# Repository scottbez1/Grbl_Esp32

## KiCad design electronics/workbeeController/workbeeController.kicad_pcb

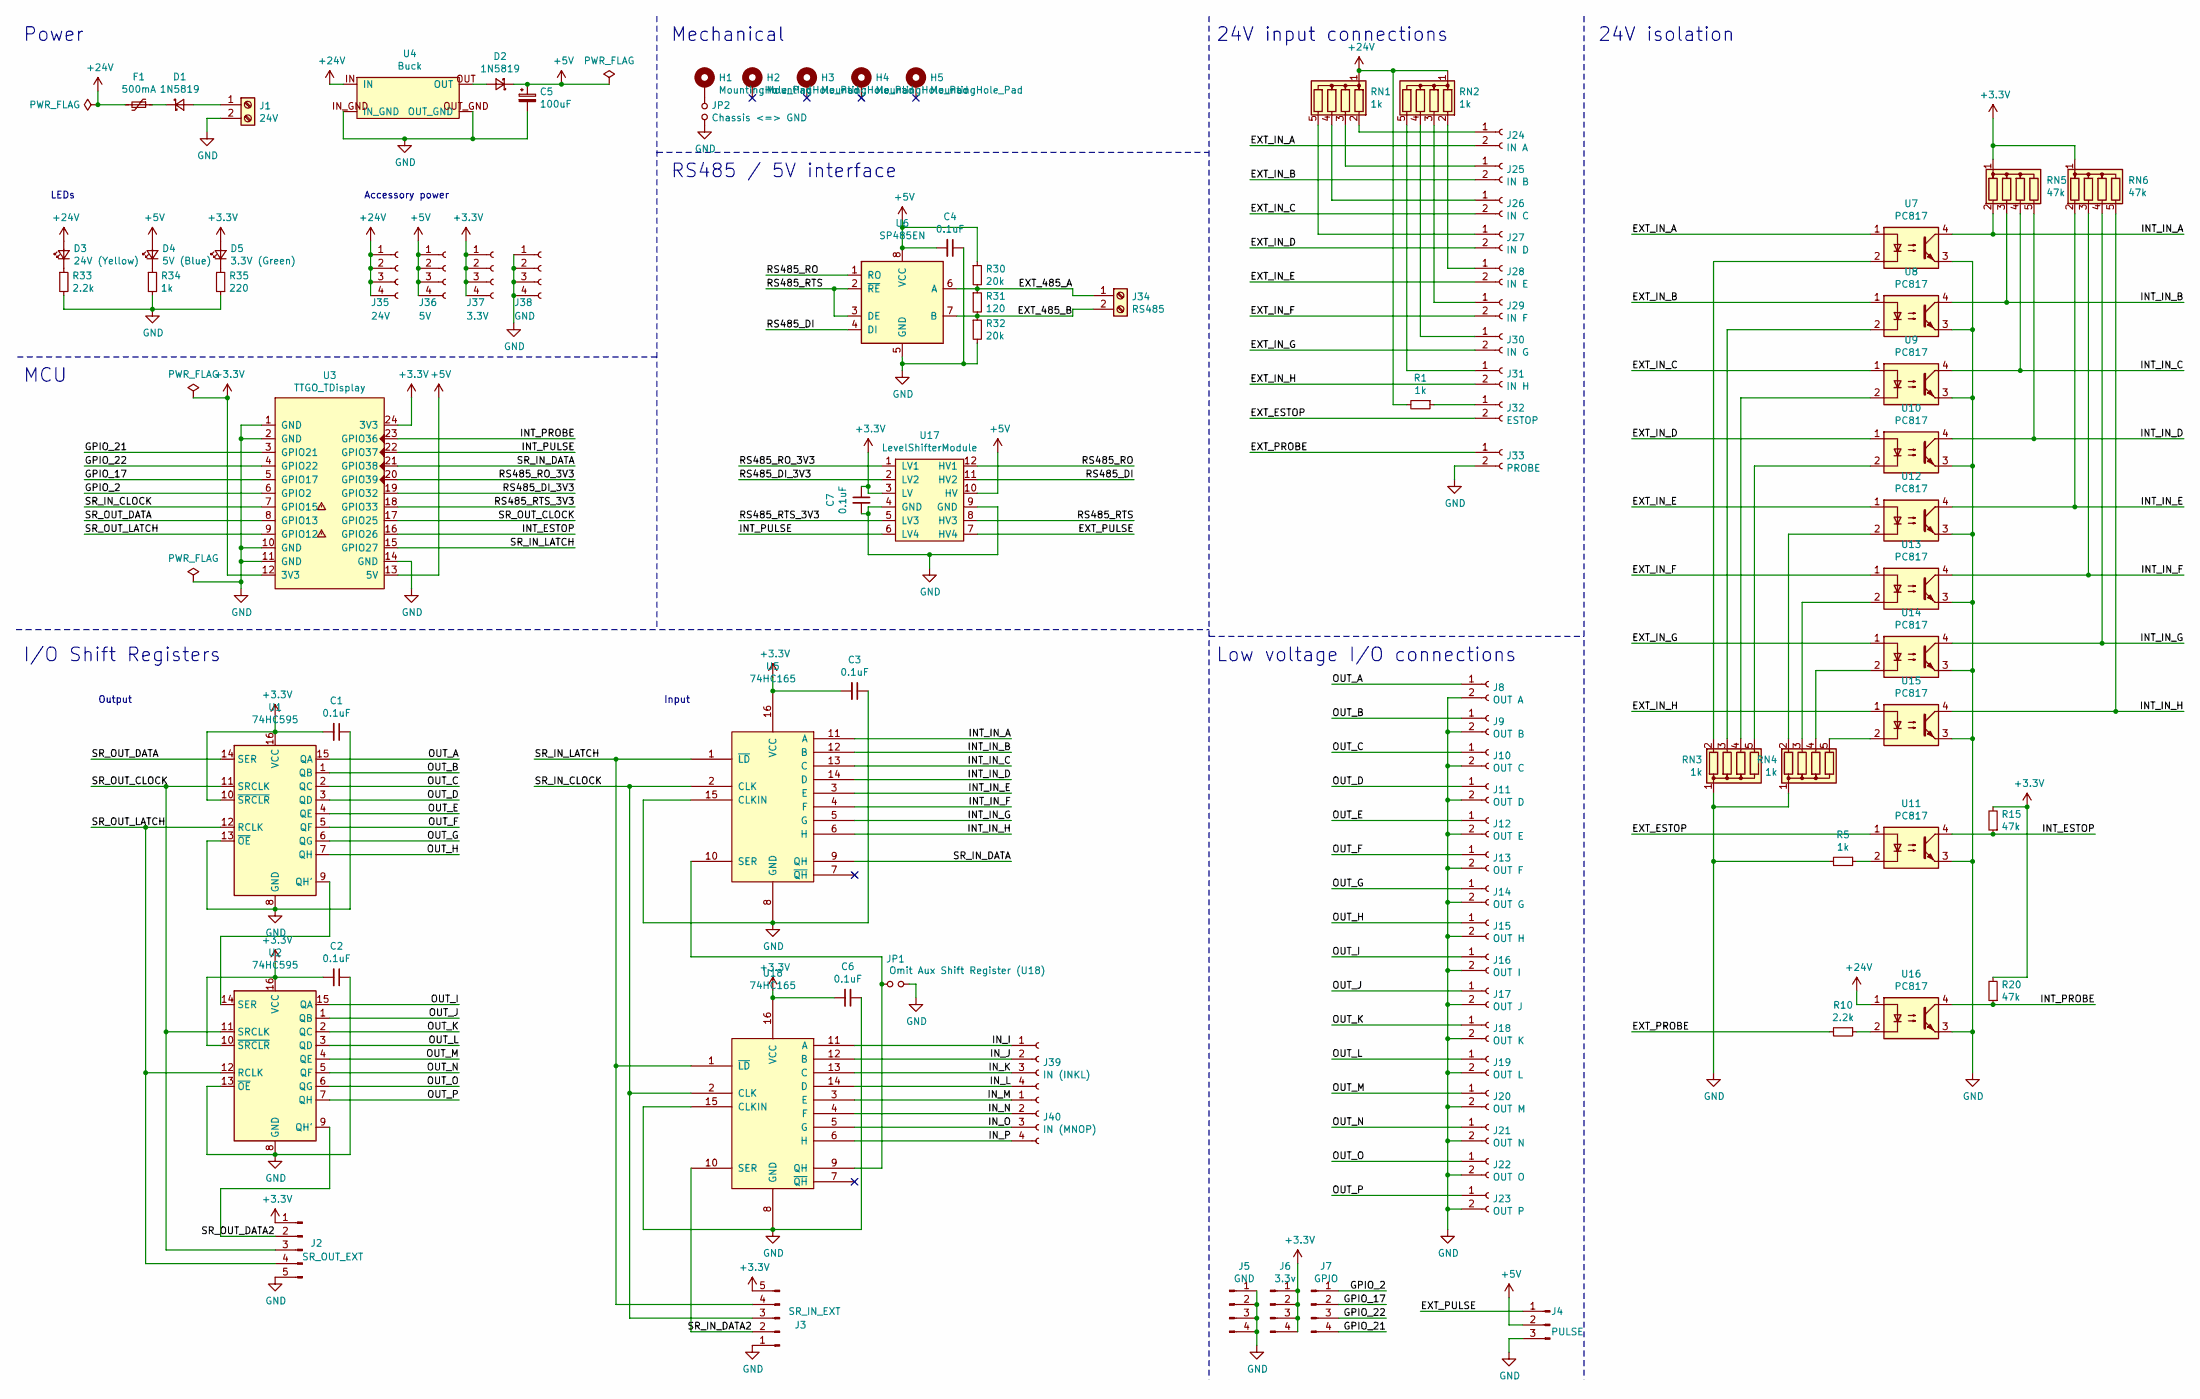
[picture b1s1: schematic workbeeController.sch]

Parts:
C1, C2, C3, C4, C6, C7: 0.1uF; C_Disc_D5.0mm_W2.5mm_P2.50mm
C5: 100uF; CP_Radial_D8.0mm_P3.50mm
D1, D2: 1N5819; D_DO-41_SOD81_P7.62mm_Horizontal
D3: 24V (Yellow); LED_D3.0mm
D4: 5V (Blue); LED_D3.0mm
D5: 3.3V (Green); LED_D3.0mm
F1: 500mA; C_Disc_D10.5mm_W5.0mm_P5.00mm
H1, H2, H3, H4, H5: MountingHole_Pad; MountingHole_4.3mm_M4_ISO7380_Pad
J1: 24V; 057-EB21A-02-D
J2: SR_OUT_EXT; PinHeader_1x05_P2.54mm_Vertical
J3: SR_IN_EXT; PinHeader_1x05_P2.54mm_Vertical
J4: PULSE; PinHeader_1x03_P2.54mm_Vertical
J5: GND; PinHeader_1x04_P2.54mm_Vertical
J6: 3.3v; PinHeader_1x04_P2.54mm_Vertical
J7: GPIO; PinHeader_1x04_P2.54mm_Vertical
J8: OUT A; PinSocket_1x02_P2.54mm_Vertical
J9: OUT B; PinSocket_1x02_P2.54mm_Vertical
J10: OUT C; PinSocket_1x02_P2.54mm_Vertical
J11: OUT D; PinSocket_1x02_P2.54mm_Vertical
J12: OUT E; PinSocket_1x02_P2.54mm_Vertical
J13: OUT F; PinSocket_1x02_P2.54mm_Vertical
J14: OUT G; PinSocket_1x02_P2.54mm_Vertical
J15: OUT H; PinSocket_1x02_P2.54mm_Vertical
J16: OUT I; PinSocket_1x02_P2.54mm_Vertical
J17: OUT J; PinSocket_1x02_P2.54mm_Vertical
J18: OUT K; PinSocket_1x02_P2.54mm_Vertical
J19: OUT L; PinSocket_1x02_P2.54mm_Vertical
J20: OUT M; PinSocket_1x02_P2.54mm_Vertical
J21: OUT N; PinSocket_1x02_P2.54mm_Vertical
J22: OUT O; PinSocket_1x02_P2.54mm_Vertical
J23: OUT P; PinSocket_1x02_P2.54mm_Vertical
J24: IN A; PinSocket_1x02_P2.54mm_Vertical
J25: IN B; PinSocket_1x02_P2.54mm_Vertical
J26: IN C; PinSocket_1x02_P2.54mm_Vertical
J27: IN D; PinSocket_1x02_P2.54mm_Vertical
J28: IN E; PinSocket_1x02_P2.54mm_Vertical
J29: IN F; PinSocket_1x02_P2.54mm_Vertical
J30: IN G; PinSocket_1x02_P2.54mm_Vertical
J31: IN H; PinSocket_1x02_P2.54mm_Vertical
J32: ESTOP; PinSocket_1x02_P2.54mm_Vertical
J33: PROBE; PinSocket_1x02_P2.54mm_Vertical
J34: RS485; 057-EB21A-02-D
J35: 24V; PinSocket_1x04_P2.54mm_Vertical
J36: 5V; PinSocket_1x04_P2.54mm_Vertical
J37: 3.3V; PinSocket_1x04_P2.54mm_Vertical
J38: GND; PinSocket_1x04_P2.54mm_Vertical
J39: IN (INKL); PinSocket_1x04_P2.54mm_Vertical
J40: IN (MNOP); PinSocket_1x04_P2.54mm_Vertical
JP1: Omit Aux Shift Register (U18); SolderJumper-2_P1.3mm_Open_TrianglePad1.0x1.5mm
JP2: Chassis <=> GND; PinHeader_1x02_P2.54mm_Vertical
R1, R5, R34: 1k; R_Axial_DIN0207_L6.3mm_D2.5mm_P7.62mm_Horizontal
R10, R33: 2.2k; R_Axial_DIN0207_L6.3mm_D2.5mm_P7.62mm_Horizontal
R15, R20: 47k; R_Axial_DIN0207_L6.3mm_D2.5mm_P7.62mm_Horizontal
R30, R32: 20k; R_Axial_DIN0207_L6.3mm_D2.5mm_P7.62mm_Horizontal
R31: 120; R_Axial_DIN0207_L6.3mm_D2.5mm_P7.62mm_Horizontal
R35: 220; R_Axial_DIN0207_L6.3mm_D2.5mm_P7.62mm_Horizontal
RN1, RN2, RN3, RN4: 1k; R_Array_SIP5
RN5, RN6: 47k; R_Array_SIP5
U1, U2: 74HC595; DIP-16_W7.62mm
U3: TTGO_TDisplay; T-DISPLAY
U4: Buck; BuckModule
U5, U18: 74HC165; DIP-16_W7.62mm
U6: SP485EN; SOIC-8_3.9x4.9mm_P1.27mm
U7, U8, U9, U10, U11, U12, U13, U14, U15, U16: PC817; DIP-4_W7.62mm
U17: LevelShifterModule

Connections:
+3V3: C1.2, C2.2, C3.2, C6.2, C7.1, D5.2 (A), J2.1, J3.5, J6.1, J6.2, J6.3, J6.4, J37.1, J37.2, J37.3, J37.4, R15.2, R20.2, RN5.1 (common), RN6.1 (common), U1.10 (~SRCLR), U1.16 (VCC), U2.10 (~SRCLR), U2.16 (VCC), U3.12 (3V3), U3.24 (3V3), U5.16 (VCC), U17.3 (LV), U18.16 (VCC)
+5V: C4.2, C5.1, D2.1 (K), D4.2 (A), J4.2, J36.1, J36.2, J36.3, J36.4, R30.1, U3.13 (5V), U6.8 (VCC), U17.10 (HV)
+24V: D3.2 (A), F1.2, J35.1, J35.2, J35.3, J35.4, R1.2, RN1.1 (common), RN2.1 (common), U4.IN, U16.1
/EXT_485_A: J34.1, R30.2, R31.1, U6.6 (A)
/EXT_485_B: J34.2, R31.2, R32.1, U6.7 (B)
/EXT_ESTOP: J32.2, U11.1
/EXT_IN_A: J24.2, U7.1
/EXT_IN_B: J25.2, U8.1
/EXT_IN_C: J26.2, U9.1
/EXT_IN_D: J27.2, U10.1
/EXT_IN_E: J28.2, U12.1
/EXT_IN_F: J29.2, U13.1
/EXT_IN_G: J30.2, U14.1
/EXT_IN_H: J31.2, U15.1
/EXT_PROBE: J33.1, R10.2
/EXT_PULSE: J4.1, U17.7 (HV4)
/GPIO_2: J7.1, U3.6 (GPIO2)
/GPIO_17: J7.2, U3.5 (GPIO17)
/GPIO_21: J7.4, U3.3 (GPIO21)
/GPIO_22: J7.3, U3.4 (GPIO22)
/INT_ESTOP: R15.1, U3.16 (GPIO26), U11.4
/INT_IN_A: RN5.2 (R1), U5.11 (A), U7.4
/INT_IN_B: RN5.3 (R2), U5.12 (B), U8.4
/INT_IN_C: RN5.4 (R3), U5.13 (C), U9.4
/INT_IN_D: RN5.5 (R4), U5.14 (D), U10.4
/INT_IN_E: RN6.2 (R1), U5.3 (E), U12.4
/INT_IN_F: RN6.3 (R2), U5.4 (F), U13.4
/INT_IN_G: RN6.4 (R3), U5.5 (G), U14.4
/INT_IN_H: RN6.5 (R4), U5.6 (H), U15.4
/INT_PROBE: R20.1, U3.23 (GPIO36), U16.4
/INT_PULSE: U3.22 (GPIO37), U17.6 (LV4)
/IN_I: J39.1, U18.11 (A)
/IN_J: J39.2, U18.12 (B)
/IN_K: J39.3, U18.13 (C)
/IN_L: J39.4, U18.14 (D)
/IN_M: J40.1, U18.3 (E)
/IN_N: J40.2, U18.4 (F)
/IN_O: J40.3, U18.5 (G)
/IN_P: J40.4, U18.6 (H)
/OUT_A: J8.1, U1.15 (QA)
/OUT_B: J9.1, U1.1 (QB)
/OUT_C: J10.1, U1.2 (QC)
/OUT_D: J11.1, U1.3 (QD)
/OUT_E: J12.1, U1.4 (QE)
/OUT_F: J13.1, U1.5 (QF)
/OUT_G: J14.1, U1.6 (QG)
/OUT_H: J15.1, U1.7 (QH)
/OUT_I: J16.1, U2.15 (QA)
/OUT_J: J17.1, U2.1 (QB)
/OUT_K: J18.1, U2.2 (QC)
/OUT_L: J19.1, U2.3 (QD)
/OUT_M: J20.1, U2.4 (QE)
/OUT_N: J21.1, U2.5 (QF)
/OUT_O: J22.1, U2.6 (QG)
/OUT_P: J23.1, U2.7 (QH)
/RS485_DI: U6.4 (DI), U17.11 (HV2)
/RS485_DI_3V3: U3.19 (GPIO32), U17.2 (LV2)
/RS485_RO: U6.1 (RO), U17.12 (HV1)
/RS485_RO_3V3: U3.20 (GPIO39), U17.1 (LV1)
/RS485_RTS: U6.2 (~RE~), U6.3 (DE), U17.8 (HV3)
/RS485_RTS_3V3: U3.18 (GPIO33), U17.5 (LV3)
/SR_IN_CLOCK: J3.3, U3.7 (GPIO15), U5.2 (CLK), U18.2 (CLK)
/SR_IN_DATA: U3.21 (GPIO38), U5.9 (QH)
/SR_IN_DATA2: J3.2, U18.10 (SER)
/SR_IN_LATCH: J3.4, U3.15 (GPIO27), U5.1 (~LD), U18.1 (~LD)
/SR_OUT_CLOCK: J2.3, U1.11 (SRCLK), U2.11 (SRCLK), U3.17 (GPIO25)
/SR_OUT_DATA: U1.14 (SER), U3.8 (GPIO13)
/SR_OUT_DATA2: J2.2, U2.9 (QH')
/SR_OUT_LATCH: J2.4, U1.12 (RCLK), U2.12 (RCLK), U3.9 (GPIO12)
GND: C1.1, C2.1, C3.1, C4.1, C5.2, C6.1, C7.2, J1.2, J2.5, J3.1, J4.3, J5.1, J5.2, J5.3, J5.4, J8.2, J9.2, J10.2, J11.2, J12.2, J13.2, J14.2, J15.2, J16.2, J17.2, J18.2, J19.2, J20.2, J21.2, J22.2, J23.2, J33.2, J38.1, J38.2, J38.3, J38.4, JP1.2, JP2.1, R5.2, R32.2, R33.2, R34.2, R35.2, RN3.1 (common), RN4.1 (common), U1.8 (GND), U1.13 (~OE), U2.8 (GND), U2.13 (~OE), U3.1 (GND), U3.2 (GND), U3.10 (GND), U3.11 (GND), U3.14 (GND), U4.IN_GND, U4.OUT_GND, U5.8 (GND), U5.15 (CLKIN), U6.5 (GND), U7.3, U8.3, U9.3, U10.3, U11.3, U12.3, U13.3, U14.3, U15.3, U16.3, U17.4 (GND), U17.9 (GND), U18.8 (GND), U18.15 (CLKIN)
unnamed: D1.1 (K), F1.1
unnamed: D1.2 (A), J1.1
unnamed: D2.2 (A), U4.OUT
unnamed: D3.1 (K), R33.1
unnamed: D4.1 (K), R34.1
unnamed: D5.1 (K), R35.1
unnamed: H1.1, JP2.2
unnamed: J24.1, RN1.2 (R1)
unnamed: J25.1, RN1.3 (R2)
unnamed: J26.1, RN1.4 (R3)
unnamed: J27.1, RN1.5 (R4)
unnamed: J28.1, RN2.2 (R1)
unnamed: J29.1, RN2.3 (R2)
unnamed: J30.1, RN2.4 (R3)
unnamed: J31.1, RN2.5 (R4)
unnamed: J32.1, R1.1
unnamed: JP1.1, U5.10 (SER), U18.9 (QH)
unnamed: R5.1, U11.2
unnamed: R10.1, U16.2
unnamed: RN3.2 (R1), U7.2
unnamed: RN3.3 (R2), U8.2
unnamed: RN3.4 (R3), U9.2
unnamed: RN3.5 (R4), U10.2
unnamed: RN4.2 (R1), U12.2
unnamed: RN4.3 (R2), U13.2
unnamed: RN4.4 (R3), U14.2
unnamed: RN4.5 (R4), U15.2
unnamed: U1.9 (QH'), U2.14 (SER)

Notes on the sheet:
Power
I/O Shift Registers
MCU
RS485 / 5V interface
24V input connections
Low voltage I/O connections
24V isolation
Accessory power
LEDs
Output
Input
Mechanical

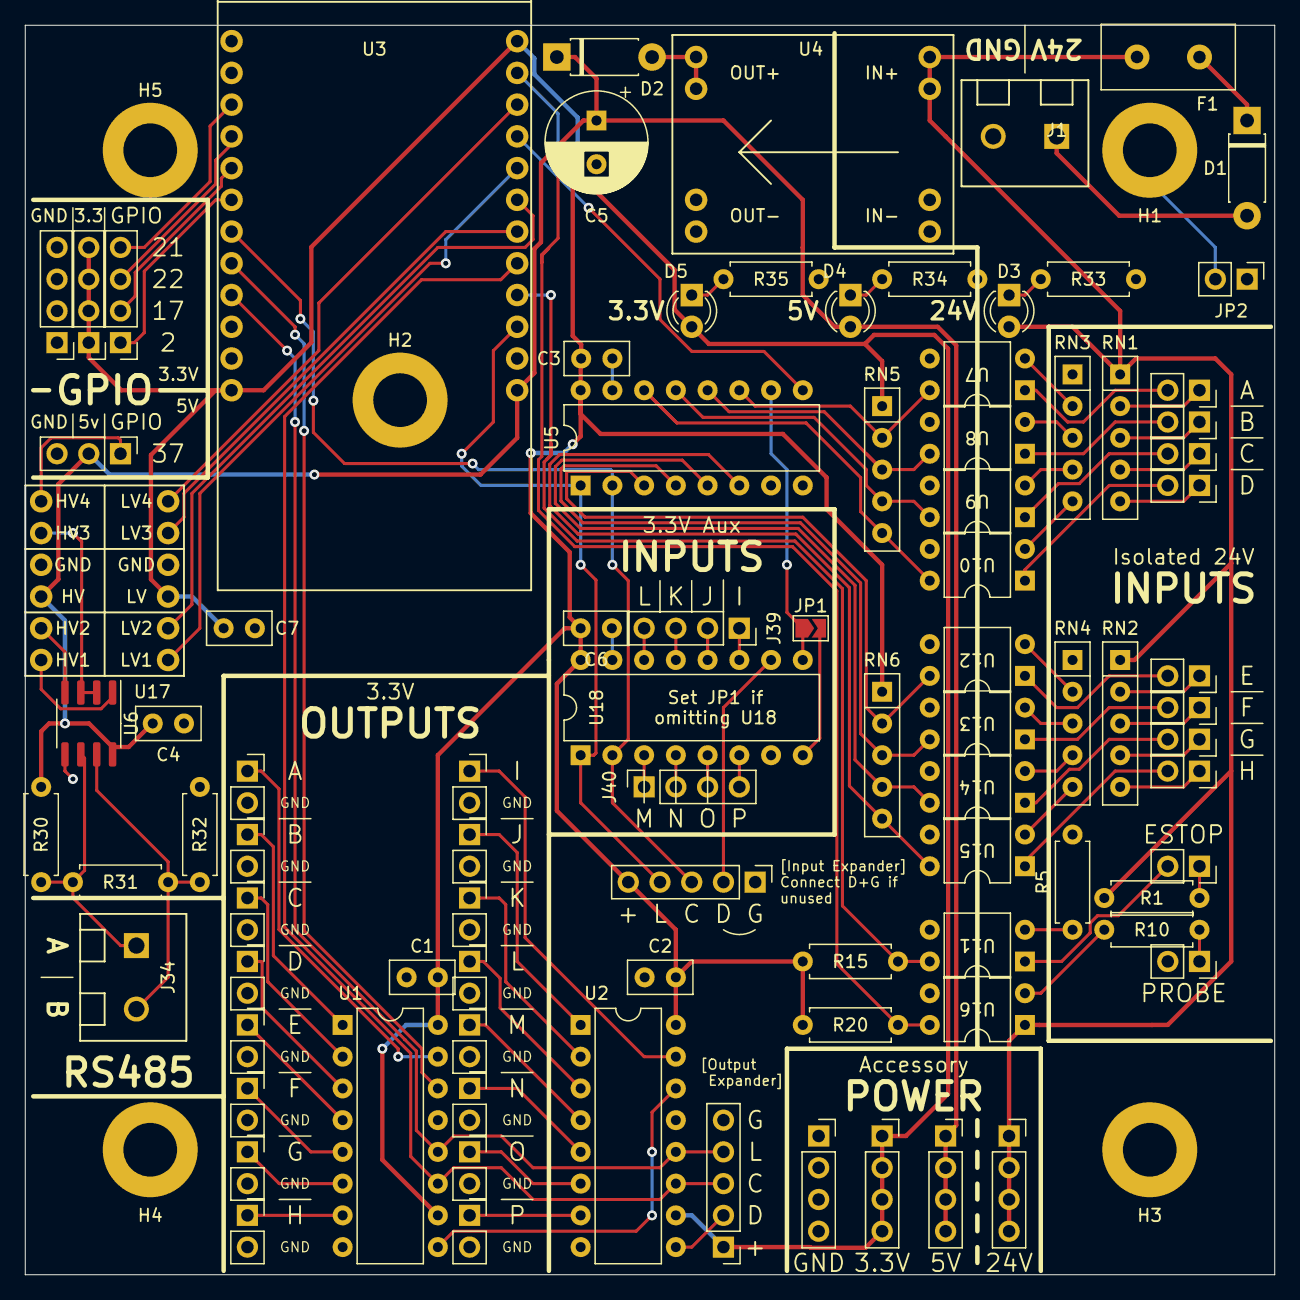
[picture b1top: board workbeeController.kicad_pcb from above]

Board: 2 copper layers, 100.0 x 100.0 mm, 95 parts (0 on the bottom side), 98 nets.

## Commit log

2020-11-29 WIP workbee configuration
2020-12-03 Add parser for actual rpm
2020-12-04 WIP spindle rewrite
2020-12-04 Working configured/actual rpm/state
2020-12-09 Mostly working
2020-12-09 Documentation updates and some cleanup
2020-12-09 Fix reverse operation
2020-12-09 Fix alarm during motion
2020-12-09 Fix crash during door
2020-12-11 Workbee machine definition
2020-12-11 Change H2A comment style to make diff smaller
2020-12-11 minor cleanup
2020-12-20 Latest workbee config
2020-12-20 ESTOP (via custom hard limit) and correct squaring
2020-12-22 Initial schematic
2020-12-23 Schematic updates
2020-12-23 SPI Shift Register Input support
2020-12-24 Basic display init
2020-12-27 Add basic flow pulse counter and shift register limits support
2020-12-27 Initial schematic and footprints complete
2020-12-28 Change to pin headers, start PCB
2020-12-29 PCB routed
2020-12-29 Change resistor footprints, add ground/chassis jumper
